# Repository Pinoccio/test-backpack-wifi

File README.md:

wifi-test-harness
=================

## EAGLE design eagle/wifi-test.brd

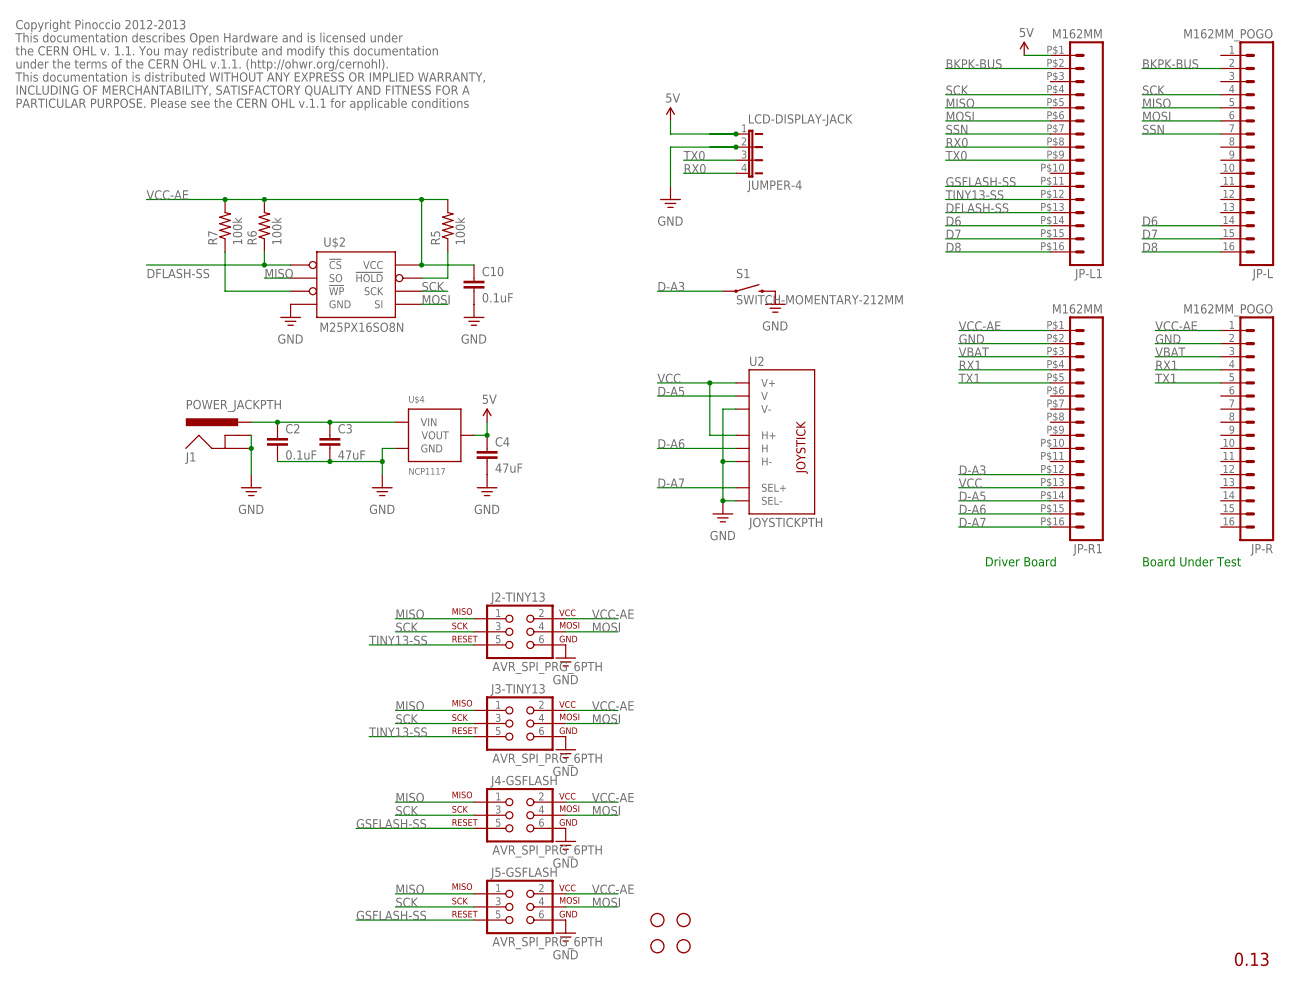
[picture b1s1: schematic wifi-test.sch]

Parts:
C2, C10: 0.1uF; 0402-CAP
C3, C4: 47uF; 0805
J1: POWER_JACKPTH; POWER_JACK_PTH
J2-TINY13, J3-TINY13, J4-GSFLASH, J5-GSFLASH: AVR_SPI_PRG_6PTH; 2X3
JP7, JP9, JP10, JP12: STAND-OFF
JP-L: M162MM_POGO; 1X16_2MM_POGO
JP-L1: M162MM; 1X16_2MM
JP-R: M162MM_POGO; 1X16_2MM_POGO
JP-R1: M162MM; 1X16_2MM
LCD-DISPLAY-JACK: JUMPER-4; 1X04
R5, R6, R7: 100k; 0402-RES
S1: SWITCH-MOMENTARY-212MM; TACTILE-PTH-12MM
U2: JOYSTICKPTH; JOYSTICK
U$2: M25PX16SO8N; SO8N
U$4: NCP1117; SOT223

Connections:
5V: C4.1, JP-L1.P$1 (1), LCD-DISPLAY-JACK.1, U$4.2 (VOUT), U$4.4 (VOUT)
BKPK-BUS: JP-L.2, JP-L1.P$2 (2)
D6: JP-L.14, JP-L1.P$14 (14)
D7: JP-L.15, JP-L1.P$15 (15)
D8: JP-L.16, JP-L1.P$16 (16)
D-A3: JP-R1.P$12 (12), S1.1
D-A5: JP-R1.P$14 (14), U2.V2 (V)
D-A6: JP-R1.P$15 (15), U2.H2 (H)
D-A7: JP-R1.P$16 (16), U2.B1A (SEL+)
DFLASH-SS: JP-L1.P$13 (13), R6.1, U$2.1 (!CS)
GND: C2.2, C3.2, C4.2, C10.2, J1.GND, J1.GNDBREAK, J2-TINY13.6, J3-TINY13.6, J4-GSFLASH.6, J5-GSFLASH.6, JP-R.2, JP-R1.P$2 (2), LCD-DISPLAY-JACK.2, S1.3 (2), U2.B2A (SEL-), U2.H3 (H-), U2.V3 (V-), U$2.4 (GND), U$4.1 (GND)
GSFLASH-SS: J4-GSFLASH.5, J5-GSFLASH.5, JP-L1.P$11 (11)
MISO: J2-TINY13.1, J3-TINY13.1, J4-GSFLASH.1, J5-GSFLASH.1, JP-L.5, JP-L1.P$5 (5), U$2.2 (SO)
MOSI: J2-TINY13.4, J3-TINY13.4, J4-GSFLASH.4, J5-GSFLASH.4, JP-L.6, JP-L1.P$6 (6), U$2.5 (SI)
unnamed: C2.1, C3.1, J1.PWR, U$4.3 (VIN)
unnamed: R7.1, U$2.3 (!WP)
unnamed: R5.1, U$2.7 (!HOLD)
RX0: JP-L1.P$8 (8), LCD-DISPLAY-JACK.4
RX1: JP-R.4, JP-R1.P$4 (4)
SCK: J2-TINY13.3, J3-TINY13.3, J4-GSFLASH.3, J5-GSFLASH.3, JP-L.4, JP-L1.P$4 (4), U$2.6 (SCK)
SSN: JP-L.7, JP-L1.P$7 (7)
TINY13-SS: J2-TINY13.5, J3-TINY13.5, JP-L1.P$12 (12)
TX0: JP-L1.P$9 (9), LCD-DISPLAY-JACK.3
TX1: JP-R.5, JP-R1.P$5 (5)
VBAT: JP-R.3, JP-R1.P$3 (3)
VCC: JP-R1.P$13 (13), U2.H1 (H+), U2.V1 (V+)
VCC-AE: C10.1, J2-TINY13.2, J3-TINY13.2, J4-GSFLASH.2, J5-GSFLASH.2, JP-R.1, JP-R1.P$1 (1), R5.2, R6.2, R7.2, U$2.8 (VCC)

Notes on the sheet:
0.13
Copyright Pinoccio 2012-2013
This documentation describes Open Hardware and is licensed under
the CERN OHL v. 1.1. You may redistribute and modify this documentation
under the terms of the CERN OHL v.1.1. (http://ohwr.org/cernohl).
This documentation is distributed WITHOUT ANY EXPRESS OR IMPLIED WARRANTY,
INCLUDING OF MERCHANTABILITY, SATISFACTORY QUALITY AND FITNESS FOR A
PARTICULAR PURPOSE. Please see the CERN OHL v.1.1 for applicable conditions
Driver Board
Board Under Test

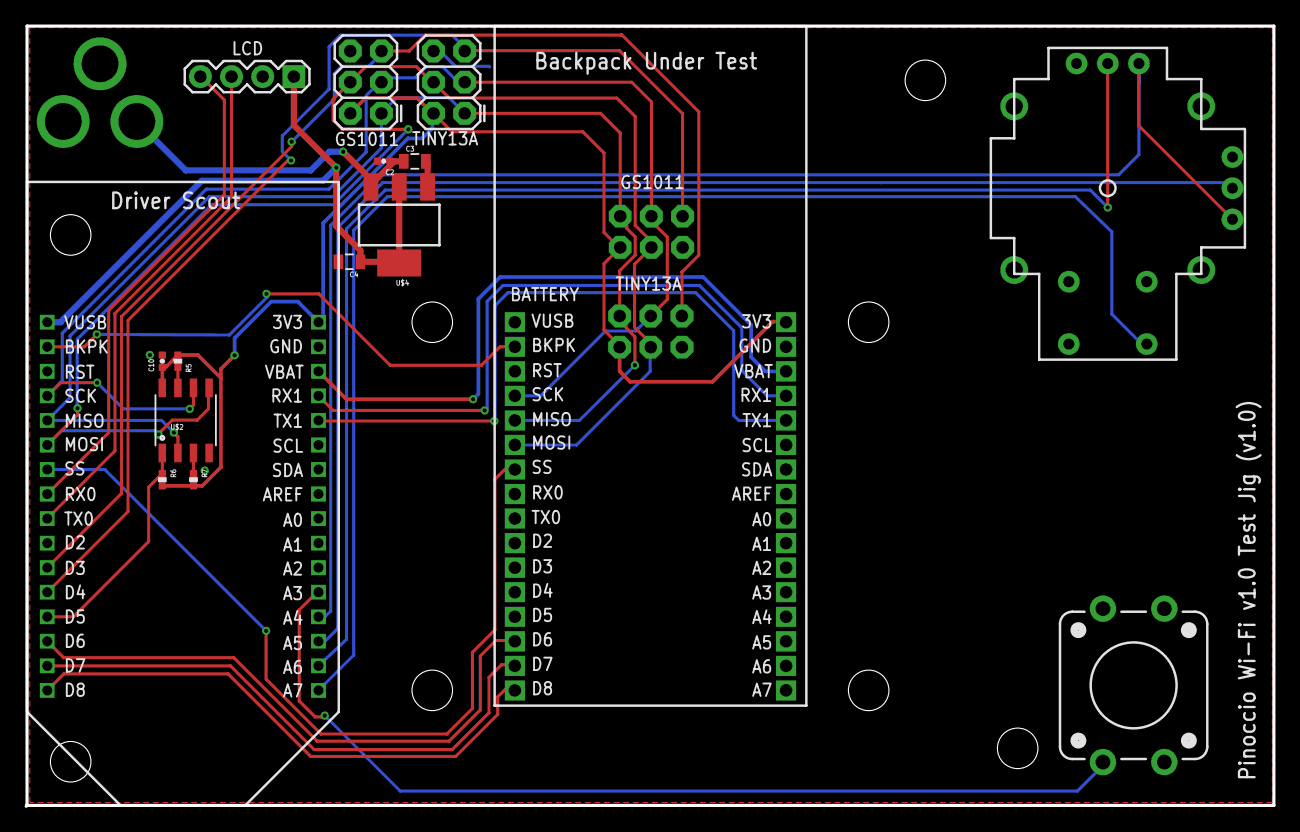
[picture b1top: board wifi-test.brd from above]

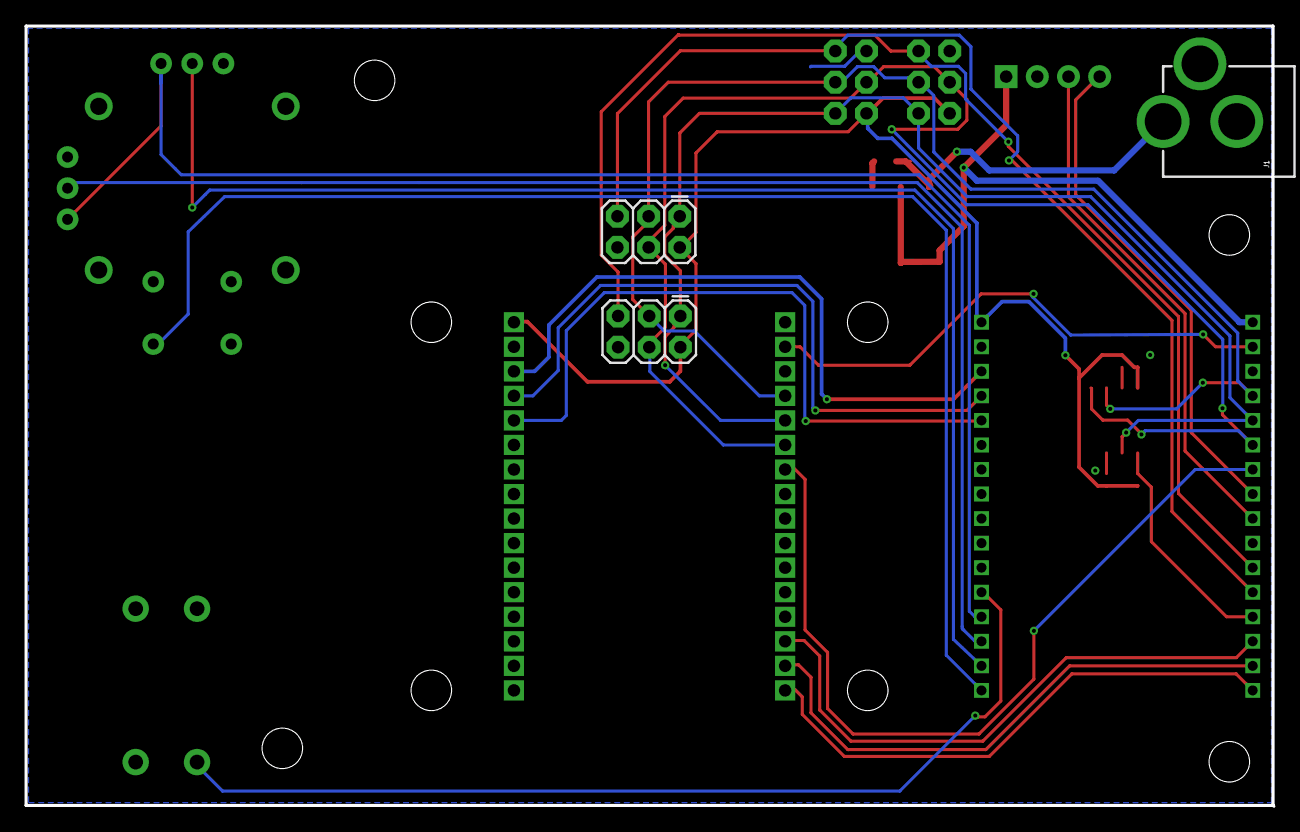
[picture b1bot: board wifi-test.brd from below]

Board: 2 copper layers, 101.7 x 63.6 mm, 29 parts (3 on the bottom side), 27 nets.

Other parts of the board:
JP8, JP11, JP13, JP14: STAND-OFF

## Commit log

2013-10-16 Initial import
2013-10-16 add gitignore
2013-10-20 Updated wifi test suite code to test almost everything. WOOP! Also adding atmega board programmer code
2013-10-20 Add python script to reverse-engineer DOS WiFi flash upgrade tool
2013-10-21 Fixed intermittent wifi flash chip write failure (removed dual calls to chip->info())
2013-10-21 Add more fixes to flash chip
2013-10-26 Got both 256RFR2 and 16U2 flashable from driver scout, big progress!
2013-11-19 Add backpack bus test support
2013-12-31 Refactor serial flash testing
2014-01-14 More Wifi test jig work--ability to write the four gainspan images to test jig driver flash
2014-01-16 Backpack bus and EEPROM now working
2014-01-18 Backpack bus flash, eeprom, checksums, and serial flash tests all completed
2014-01-26 Final fixups for wifi test jigs
2014-02-17 In md5.c, include string.h for memcpy
    This prevents a compiler warning
2014-02-17 Use the Backpacks class for testing the backpack bus
    The PBBP interface has changed, making it less suitable for doing these
    tests. Instead, the Backpacks class provides an even easier interface,
    so use that.
2014-02-17 Use the Pbbe class for checksum calculations
    The crc functions previously used are no longer available under this
    name and using the functions from Pbbe removes the need to hardcode the
    CRC parameters in this code.
2014-02-20 Modify test code only for post-Gainspan testing
2014-03-05 Clean up SPI chip select, fix SPI speed
2014-03-26 Slowed down the SPI clock for better reliability
2014-04-30 Add update wifi firmware
2014-05-02 updated middle board hole size
2014-05-23 Fix RgbLed to Led
2014-06-11 Add longer timeout between PGM/RUN states
2014-06-11 Update serial numbers and RgbLed->Led fix
2014-06-11 Update attiny13 eeprom map to v1.1 for additional RDY pin
2014-06-30 Whitespace fix
2016-03-17 Added some fixes to ensure SPI is shut off (for Gainspan serial flash init from gs_flashprogram.exe)

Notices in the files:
eagle/wifi-test.brd:
Licensed under CERN OHL v.1.1
